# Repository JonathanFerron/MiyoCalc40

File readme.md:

# MiyoCalc40

RPN calculator

This is a project for a trough-hole only RPN calculator with a flexible configuration. The idea is for it to be minimalist, meant as a complement to other tools that the 
user would typically have on hand (computer, formula cheat sheet, etc.) rather than as a replacement, and made with easy to solder through-hole components.

I would like to give credit to the work of the following individuals which has served as inspiration for this project:

- Alex Garza for work done on the Voyager form-factor RPN calculators: https://paxer.net/voyager/
- Anton Poluektov for work done on the OpenRPNCalc calculator: https://github.com/apoluekt/OpenRPNCalc

## Building and flashing the firmware

Toolchain: `avr-gcc` + avr-libc (AVR128DA28 support built in) and avrdude 8.x. No Arduino IDE needed.
Programmer: a CH340E USB-serial adapter used as a SerialUPDI programmer (avrdude's `serialupdi`).

From `MiyoCalc40_firmware/`:

| Command | Action |
|---|---|
| `make` | Build `build/MiyoCalc40_firmware.hex` |
| `make flash` | Flash the firmware over UPDI |
| `make flash_fuses` | Write the fuse row (first-time setup, or after changing `avrducore/fuses.c`) |
| `make help` | List all targets |

The default port is `/dev/ttyUSB0`. To use a different one, pass `PROG_PORT`, e.g. `make flash PROG_PORT=/dev/ttyUSB1`.

Equivalent raw avrdude command:

    avrdude -c serialupdi -p avr128da28 -P /dev/ttyUSB0 -U flash:w:build/MiyoCalc40_firmware.hex:i

The MiyoCalc40 **PCB work** is licensed under a
[Creative Commons Attribution-NonCommercial-ShareAlike 4.0 International License][cc-by-nc-sa].

[![CC BY-NC-SA 4.0][cc-by-nc-sa-image]][cc-by-nc-sa]

[cc-by-nc-sa]: http://creativecommons.org/licenses/by-nc-sa/4.0/
[cc-by-nc-sa-image]: https://licensebuttons.net/l/by-nc-sa/4.0/88x31.png
[cc-by-nc-sa-shield]: https://img.shields.io/badge/License-CC%20BY--NC--SA%204.0-lightgrey.svg

The MiyoCalc40 **Firmware** is licensed under the GNU General Public License version 3:
Copyright (C) 2026 Jonathan Ferron

This program is free software: you can redistribute it and/or modify
it under the terms of the GNU General Public License as published by
the Free Software Foundation, either version 3 of the License, or (at your option) any later version.

This program is distributed in the hope that it will be useful,
but WITHOUT ANY WARRANTY; without even the implied warranty of
MERCHANTABILITY or FITNESS FOR A PARTICULAR PURPOSE.  See the
GNU General Public License for more details.

You should have received a copy of the GNU General Public License
along with this program.  If not, see <http://www.gnu.org/licenses/>.

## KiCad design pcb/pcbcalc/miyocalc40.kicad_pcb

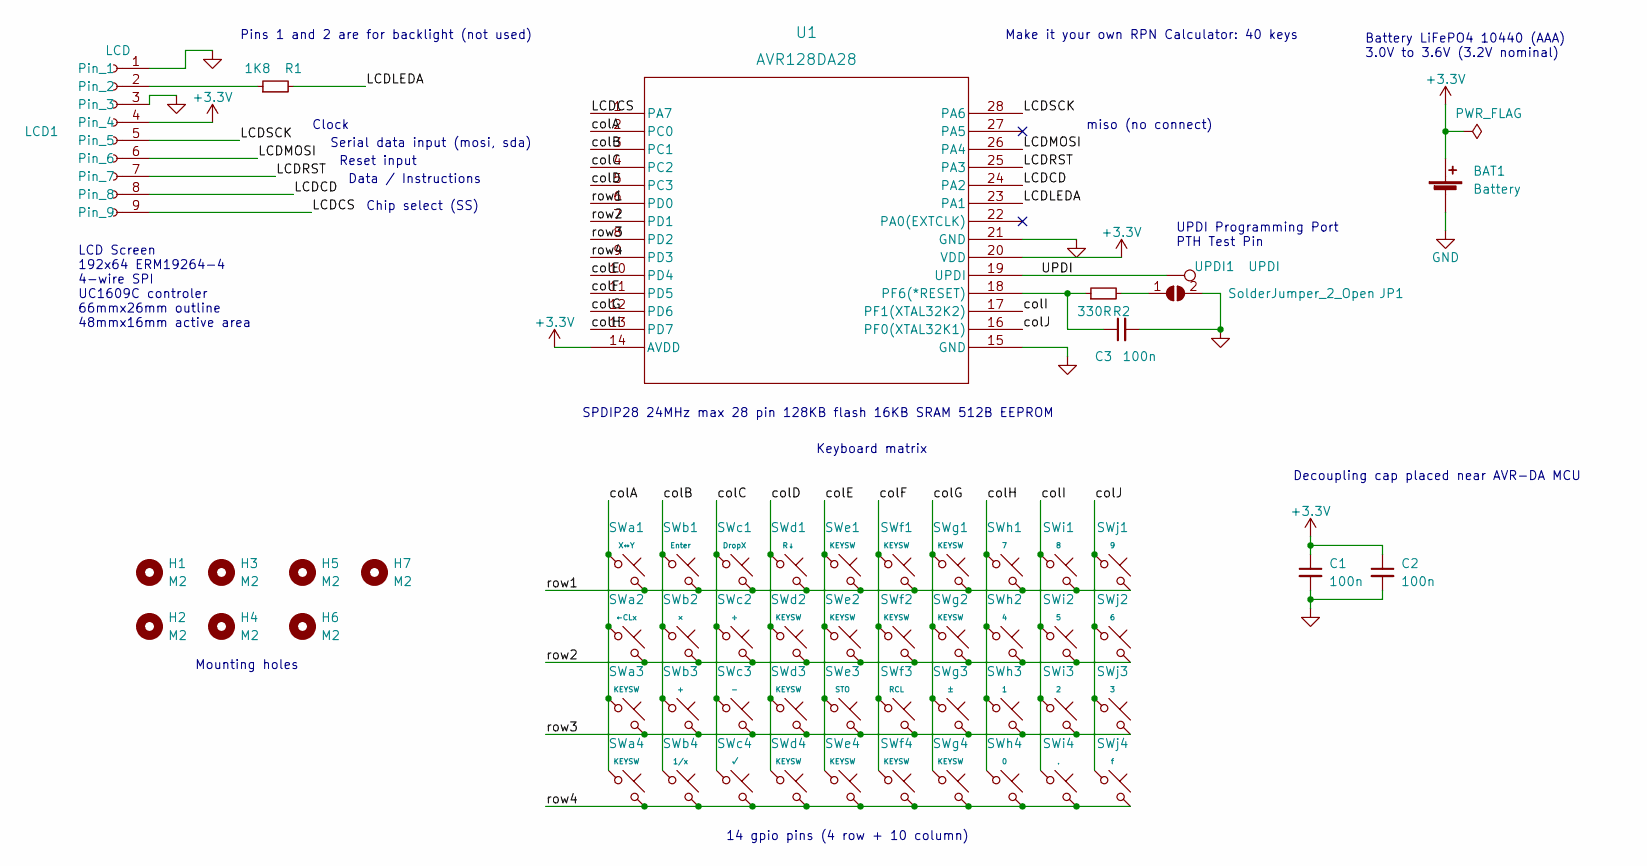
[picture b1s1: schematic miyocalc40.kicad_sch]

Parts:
BAT1: Battery; BatteryHolder_AAA
C1, C2, C3: 100n; C_Disc_D4.3mm_W1.9mm_P5.00mm
H1, H2, H3, H4, H5, H6, H7: M2; MountingHole
JP1: SolderJumper_2_Open; Reset Jumper
LCD1: LCD; PinSocket_1x09_P2.54mm_Vertical
R1: 1K8; R_Axial_DIN0204_L3.6mm_D1.6mm_P5.08mm_Horizontal
R2: 330R; R_Axial_DIN0204_L3.6mm_D1.6mm_P5.08mm_Horizontal
SWa1: X↔Y; SW_PUSH_6mm
SWa2: ←CLx; SW_PUSH_6mm
SWa3, SWa4: KEYSW; SW_PUSH_6mm
SWb1: Enter; SW_PUSH_6mm
SWb2: ×; SW_PUSH_6mm
SWb3: +; SW_PUSH_6mm
SWb4: 1/x; SW_PUSH_6mm
SWc1: DropX; SW_PUSH_6mm
SWc2: ÷; SW_PUSH_6mm
SWc3: -; SW_PUSH_6mm
SWc4: √; SW_PUSH_6mm
SWd1: R↓; SW_PUSH_6mm
SWd2, SWd3, SWd4: KEYSW; SW_PUSH_6mm
SWe1, SWe2, SWe4: KEYSW; SW_PUSH_6mm
SWe3: STO; SW_PUSH_6mm
SWf1, SWf2, SWf4: KEYSW; SW_PUSH_6mm
SWf3: RCL; SW_PUSH_6mm
SWg1, SWg2, SWg4: KEYSW; SW_PUSH_6mm
SWg3: ±; SW_PUSH_6mm
SWh1: 7; SW_PUSH_6mm
SWh2: 4; SW_PUSH_6mm
SWh3: 1; SW_PUSH_6mm
SWh4: 0; SW_PUSH_6mm
SWi1: 8; SW_PUSH_6mm
SWi2: 5; SW_PUSH_6mm
SWi3: 2; SW_PUSH_6mm
SWi4: .; SW_PUSH_6mm
SWj1: 9; SW_PUSH_6mm
SWj2: 6; SW_PUSH_6mm
SWj3: 3; SW_PUSH_6mm
SWj4: f; SW_PUSH_6mm
U1: AVR128DA28; DIP-28_W7.62mm_Socket
UPDI1: UPDI; UPDI Port

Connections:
+3V3: BAT1.1 (+), C1.1, C2.1, LCD1.4, U1.14 (AVDD), U1.20 (VDD)
/LCDCD: LCD1.8, U1.24 (PA2)
/LCDCS: LCD1.9, U1.1 (PA7)
/LCDLEDA: R1.2, U1.23 (PA1)
/LCDMOSI: LCD1.6, U1.26 (PA4)
/LCDRST: LCD1.7, U1.25 (PA3)
/LCDSCK: LCD1.5, U1.28 (PA6)
/UPDI: U1.19 (UPDI), UPDI1.1
/colA: SWa1.1, SWa2.1, SWa3.1, SWa4.1, U1.2 (PC0)
/colB: SWb1.1, SWb2.1, SWb3.1, SWb4.1, U1.3 (PC1)
/colC: SWc1.1, SWc2.1, SWc3.1, SWc4.1, U1.4 (PC2)
/colD: SWd1.1, SWd2.1, SWd3.1, SWd4.1, U1.5 (PC3)
/colE: SWe1.1, SWe2.1, SWe3.1, SWe4.1, U1.10 (PD4)
/colF: SWf1.1, SWf2.1, SWf3.1, SWf4.1, U1.11 (PD5)
/colG: SWg1.1, SWg2.1, SWg3.1, SWg4.1, U1.12 (PD6)
/colH: SWh1.1, SWh2.1, SWh3.1, SWh4.1, U1.13 (PD7)
/colI: SWi1.1, SWi2.1, SWi3.1, SWi4.1, U1.17 (PF1(XTAL32K2))
/colJ: SWj1.1, SWj2.1, SWj3.1, SWj4.1, U1.16 (PF0(XTAL32K1))
/row1: SWa1.2, SWb1.2, SWc1.2, SWd1.2, SWe1.2, SWf1.2, SWg1.2, SWh1.2, SWi1.2, SWj1.2, U1.6 (PD0)
/row2: SWa2.2, SWb2.2, SWc2.2, SWd2.2, SWe2.2, SWf2.2, SWg2.2, SWh2.2, SWi2.2, SWj2.2, U1.7 (PD1)
/row3: SWa3.2, SWb3.2, SWc3.2, SWd3.2, SWe3.2, SWf3.2, SWg3.2, SWh3.2, SWi3.2, SWj3.2, U1.8 (PD2)
/row4: SWa4.2, SWb4.2, SWc4.2, SWd4.2, SWe4.2, SWf4.2, SWg4.2, SWh4.2, SWi4.2, SWj4.2, U1.9 (PD3)
GND: BAT1.2 (-), C1.2, C2.2, C3.2, JP1.2 (B), LCD1.1, LCD1.3, U1.15 (GND), U1.21 (GND)
unnamed: C3.1, R2.1, U1.18 (PF6(*RESET))
unnamed: JP1.1 (A), R2.2
unnamed: LCD1.2, R1.1

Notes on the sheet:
Pins 1 and 2 are for backlight (not used)
miso (no connect)
Battery LiFePO4 10440 (AAA) 3.0V to 3.6V (3.2V nominal)
Decoupling cap placed near AVR-DA MCU
Clock
Make it your own RPN Calculator: 40 keys
Data / Instructions
Reset input
14 gpio pins (4 row + 10 column)
LCD Screen 192x64 ERM19264-4 4-wire SPI UC1609C controler 66mmx26mm outline 48mmx16mm active area
UPDI Programming Port PTH Test Pin
Serial data input (mosi, sda)
Keyboard matrix
Mounting holes
SPDIP28 24MHz max 28 pin 128KB flash 16KB SRAM 512B EEPROM
Chip select (SS)

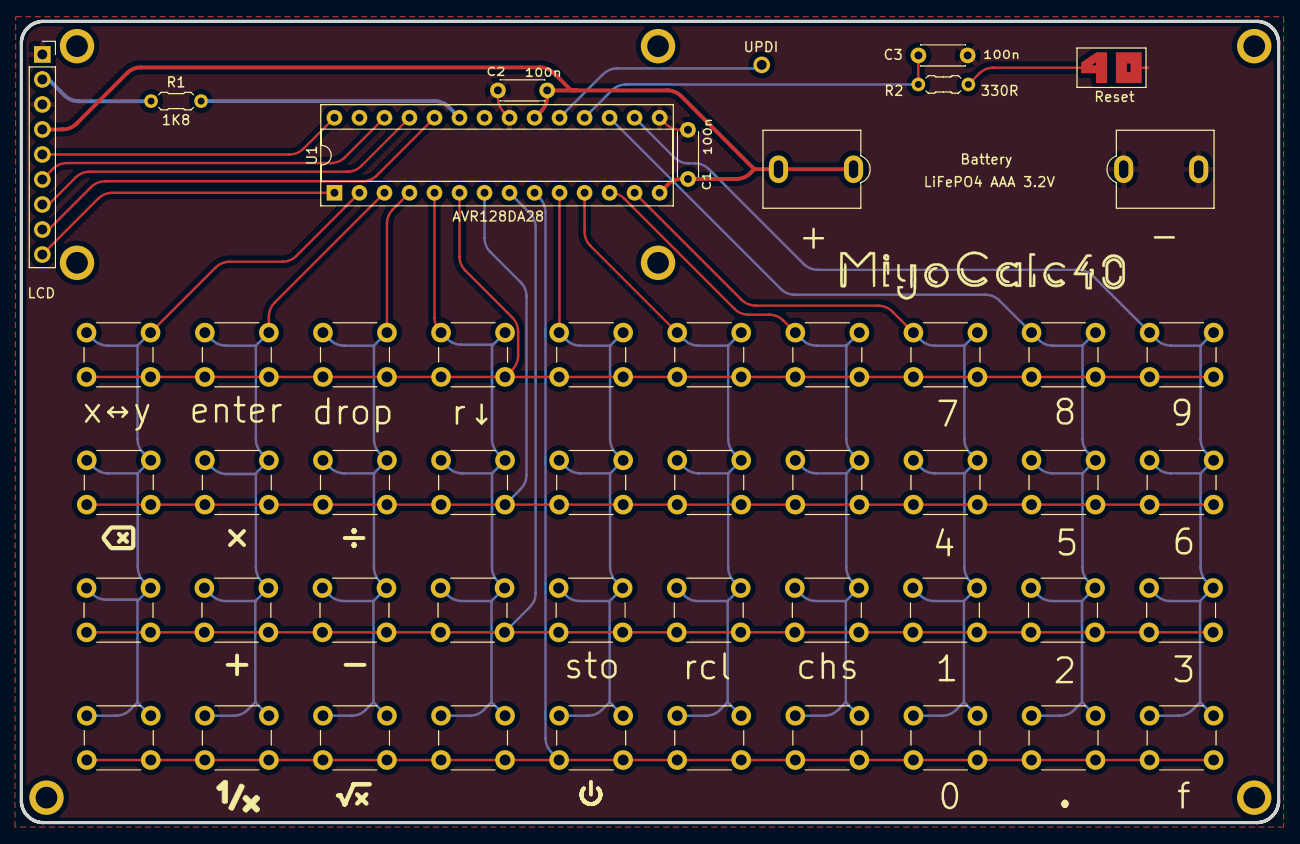
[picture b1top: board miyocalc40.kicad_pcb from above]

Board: 2 copper layers, 127.7 x 81.4 mm, 57 parts (0 on the bottom side), 26 nets.

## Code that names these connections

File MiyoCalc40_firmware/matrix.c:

/* Matrix scanning examples:

1. Open RPN Calc: slower but more robust
define number_of_columns and number_of_rows
declare const for row pin and column pin arrays (contain pin numbers)

helper function (scan keyboard), returns an uint16_t, takes no argument
  pressed_row = 0
  pressed_column = -1
  set all output column pins to high
  scan columns: for each column
  	set one column pin output low
  	small 10 microsecond delay for transitional processes to finish
  	read row pins: for each row
  		read row pin status
  		if row pin is low:
  			pressed_row = current row
  			pressed_column = current column
  	end loop over all rows

  	set column pin back to high

  end loop over all columns

  reset all output column pins to low

  return pressed_column + pressed_row * number_of_columns + 1

2. an3407: faster but less robust
define number_of_columns and number_of_rows
declare const for row pin and column pin arrays (contain pin numbers)

set column as input pull-up (already done in main loop)
Rows as output low (already done in main loop)
Read each column to find which has been pulled low
This will tell us which column was pressed

set row pins as input pull-up
Set entire column axis as output low
Read voltage on each rows to find which has been pulled low
This will tell us which row was pressed

reset columns pins to input pull-up and row pins as output low

Combine row and column into an int (e.g. 2 nibbles encoded in an uint8) or a set of 2 ints (one for each value, could be in a bitfield) and return the result

*/

// Includes
#include "matrix.h"
#include "Arduino.h"

// Defines
//define number_of_columns and number_of_rows

// Global variables
//declare const for row pin and column pin arrays (contain pin numbers)
const uint8_t row_pin_array[NUM_ROW_PINS] = {
		PIN_PD0, PIN_PD1, PIN_PD2, PIN_PD3};

const uint8_t column_pin_array[NUM_COLUMN_PINS] = {
		PIN_PC0, PIN_PC1, PIN_PC2, PIN_PC3, PIN_PD4, PIN_PD5, PIN_PD6, PIN_PD7, PIN_PF1, PIN_PF0};
    
const uint8_t unused_pin_array[2] = {PIN_PA5, PIN_PA0};

uint8_t keypos_r;
uint8_t keypos_c;
/*
struct keyposS
{
  unsigned int r : 4;
  unsigned int c : 4;
} keypos;
*/

// helper matrix scanning functions code

void setupMatrix()
{
  // set-up pull-up on column and row pins
  PORTA.PINCONFIG = PORT_PULLUPEN_bm;  
  PORTC.PINCTRLSET = 0b00001111;
  PORTD.PINCTRLSET = 0b11111111;
  PORTF.PINCTRLSET = 0b00000011;
  
  // set-up column pins as input 
  //PORTC.DIR &= ~(PIN0_bm | PIN1_bm | PIN2_bm | PIN3_bm); 
  //PORTD.DIR &= ~(PIN4_bm | PIN5_bm | PIN6_bm | PIN7_bm); 
  //PORTF.DIR &= ~(PIN0_bm, PIN1_bm); 
  PORTC.DIRCLR = PIN0_bm | PIN1_bm | PIN2_bm | PIN3_bm;
  PORTD.DIRCLR = PIN4_bm | PIN5_bm | PIN6_bm | PIN7_bm;
  PORTF.DIRCLR = PIN0_bm | PIN1_bm;
  
  // set row pins as output low
  //PORTD.DIR |= PIN0_bm | PIN1_bm | PIN2_bm | PIN3_bm; // output
  //PORTD.OUT &= ~(PIN0_bm | PIN1_bm | PIN2_bm | PIN3_bm); // low
  PORTD.DIRSET = PIN0_bm | PIN1_bm | PIN2_bm | PIN3_bm;
  PORTD.OUTCLR = PIN0_bm | PIN1_bm | PIN2_bm | PIN3_bm;

  // Disable the digital input buffer on the unused pins (porta.pin0ctrl = port_pullupen_bm | port_isc_input_disable_gc)
  PORTA.PINCONFIG = PORT_PULLUPEN_bm | PORT_ISC_INPUT_DISABLE_gc;
  PORTA.PINCTRLSET = 0b00100001;
  
  keypos_r = 0xff;  // initialize keypos to 'null', which we'll define as 0xff by convention
  keypos_c = 0xff;
}

/*
Read each column to find which has been pulled low
This will tell us which column was pressed

Set column pins as output low
set row pins as input

Read each row to find which has been pulled low
This will tell us which row was pressed

reset columns pins to input and row pins as output low

Combine row and column into a keypos struct and return the result (global var keypos)
*/
void scanKB()
{
  // read each column to find if one has been pulled low
  // TODO: if necessary, look into optimizing this loop: could use digitalReadFast() if we were to unroll the loop to use constant pin numbers. 
  // It does make the code harder to modify after, however.
  for (uint8_t col = 0; col < NUM_COLUMN_PINS; col++)  
  {
    if ( digitalRead(column_pin_array[col]) == LOW )  
    {
      // we now know that 'c' is the column of the button pressed      
      
      // set column pins as output low
      PORTC.DIRTGL = PIN0_bm | PIN1_bm | PIN2_bm | PIN3_bm;  // toggle direction to output
      PORTD.DIRTGL = PIN4_bm | PIN5_bm | PIN6_bm | PIN7_bm;
      PORTF.DIRTGL = PIN0_bm | PIN1_bm;
      
      PORTC.OUTCLR = PIN0_bm | PIN1_bm | PIN2_bm | PIN3_bm;  // low: can this be optimized out by running it just once in setupMatrix() ?
      PORTD.OUTCLR = PIN4_bm | PIN5_bm | PIN6_bm | PIN7_bm;
      PORTF.OUTCLR = PIN0_bm | PIN1_bm;
      
      // set row pins as input
      PORTD.DIRTGL = PIN0_bm | PIN1_bm | PIN2_bm | PIN3_bm;
      
      // Read each row to find which has been pulled low
      for (uint8_t row = 0; row < NUM_ROW_PINS; row++)
      {
        if ( digitalRead(row_pin_array[row]) == LOW )
        {
          // we now know that 'r' is the row of the button pressed
          // Combine row and column into a keypos struct and return the result (global var keypos)         
          keypos_c = col;  // there is a cast from 8 to 4 bit here
          keypos_r = row;
          break;  // break out of the loop across each row
        }  // if a row pin was low        
        
      } // loop across each row
      
      // reset columns pins to input and row pins as output low
      // column pins
      PORTC.DIRTGL = PIN0_bm | PIN1_bm | PIN2_bm | PIN3_bm;  // toggle direction to input
      PORTD.DIRTGL = PIN4_bm | PIN5_bm | PIN6_bm | PIN7_bm;
      PORTF.DIRTGL = PIN0_bm | PIN1_bm;
      
      // row pins
      PORTD.DIRTGL = PIN0_bm | PIN1_bm | PIN2_bm | PIN3_bm; // toggle direction to output
      PORTD.OUTCLR = PIN0_bm | PIN1_bm | PIN2_bm | PIN3_bm; // low: can this be optimized out as well?
      
      break;  // break out of the loop across each column
    } // if a column pin was low
    
  } // loop across each column
  
} // scanKB()

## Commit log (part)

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2023-08-17 Refactoring of LCD code
2023-08-17 Code matrix scanning methods.
2023-08-17 PCB updates, mostly silkscreen tweaking
2023-08-17 Work on LCD functionalities
2023-08-20 PWM for backlight
2023-08-31 Several updates to firmware
2023-08-31 Small updates to pcb
2023-09-01 small documentation updates
2023-09-25 Multiple updates for rev 1.0
2023-10-07 Multiple updates to firmware
2023-10-18 Further implement calc functionalities
2023-10-24 Prep work for config menus
2023-10-31 Prep work for config and programming mode
2023-11-07 Prep work for programming mode
2023-11-10 set trig mode
2023-11-20 prep config mode
2023-12-22 update precision
2025-07-17 Change precision
2026-04-07 simplify code
